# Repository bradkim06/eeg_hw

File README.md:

# Project Goal

기존 외주 뇌파모듈을 더 좋은 성능과 가격으로 대체

## Schematic

[v0.2-dev](./doc/eeg.pdf)

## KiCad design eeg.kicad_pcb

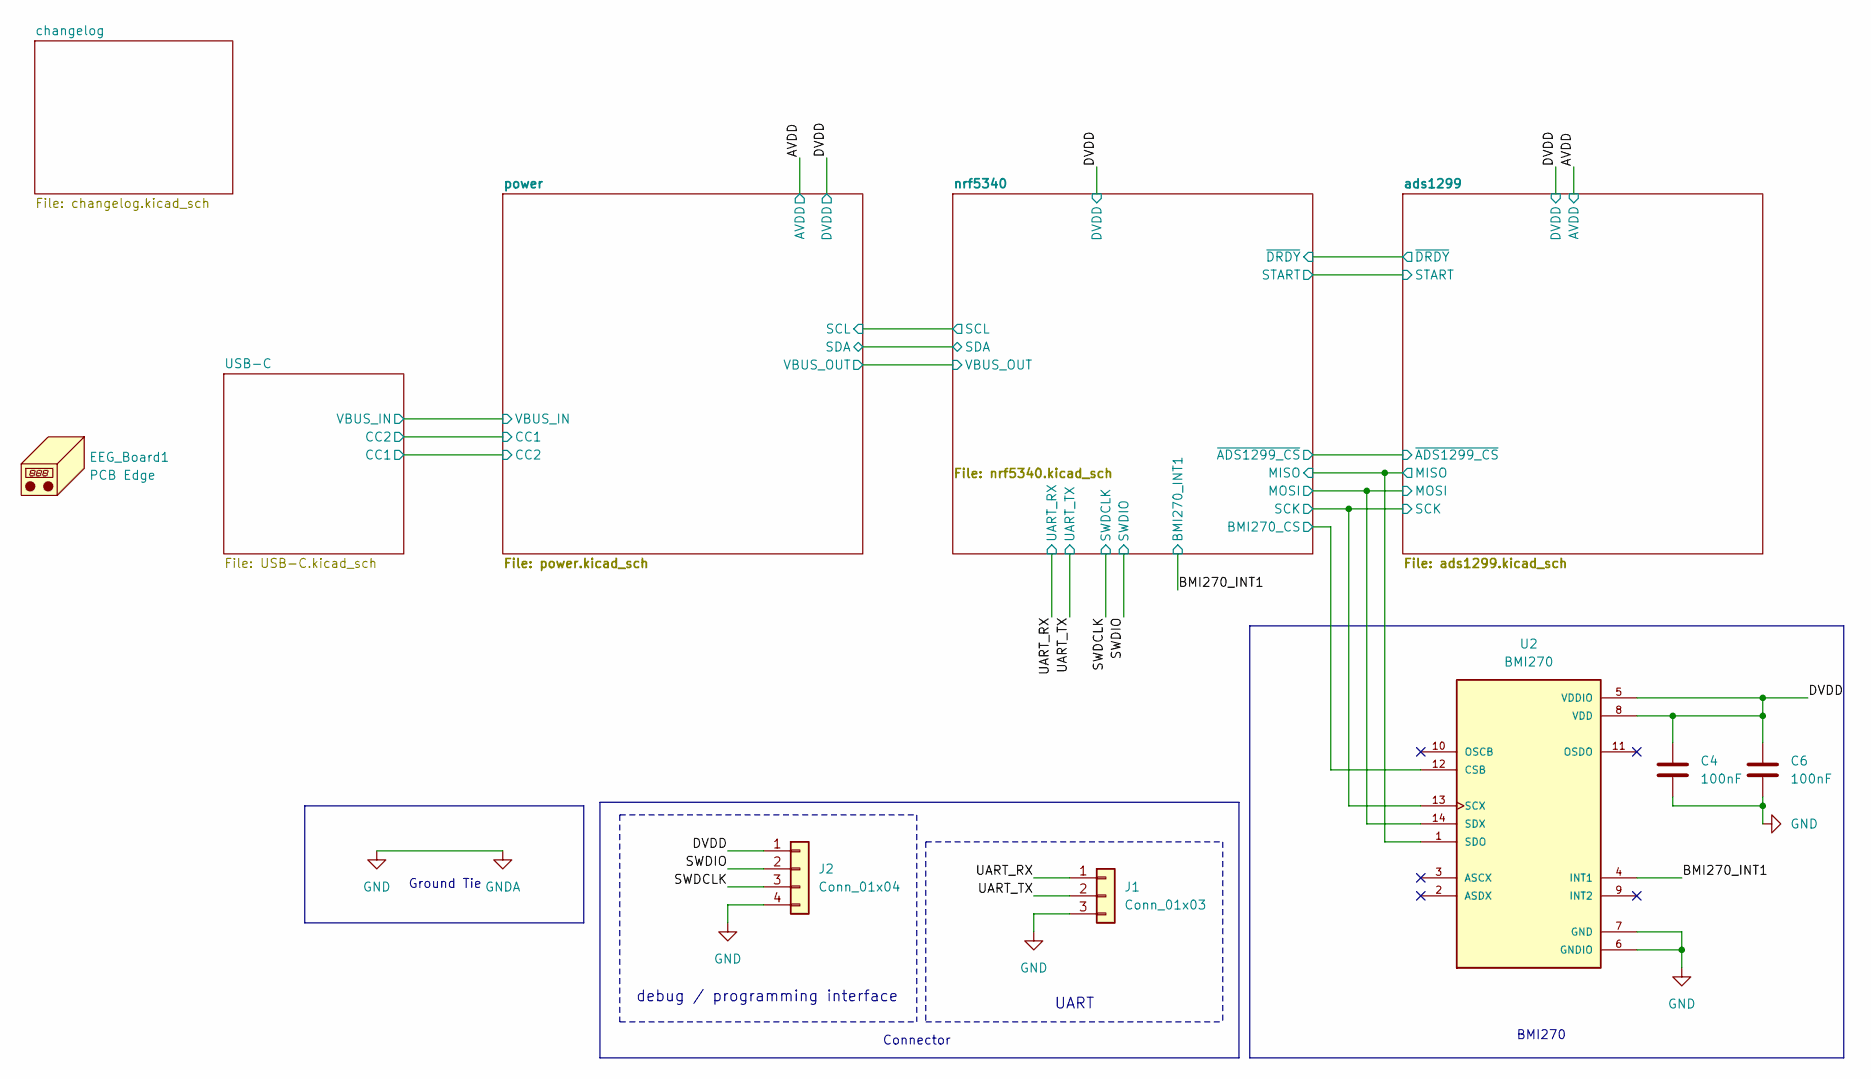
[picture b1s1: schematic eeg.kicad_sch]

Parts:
C4, C6: 100nF; C_0402_1005Metric; MANUFACTURER_PART_NUMBER GRM155R71C104KA88D
EEG_Board1: PCB Edge; eeg
J1: Conn_01x03; PinHeader_1x03_P2.54mm_Vertical; MANUFACTURER_PART_NUMBER 1.25T-3A
J2: Conn_01x04; PinHeader_1x04_P2.54mm_Vertical; MANUFACTURER_PART_NUMBER 1.25T-4A
U2: BMI270; XDCR_BMI270; MANUFACTURER_PART_NUMBER BMI270

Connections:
/BMI270_INT1: U2.4 (INT1); also elsewhere on the board
/DVDD: C4.1, C6.1, J2.1, U2.5 (VDDIO), U2.8 (VDD); also elsewhere on the board
/SWDCLK: J2.3; also elsewhere on the board
/SWDIO: J2.2; also elsewhere on the board
/UART_RX: J1.1; also elsewhere on the board
/UART_TX: J1.2; also elsewhere on the board
/ads1299/MISO: U2.1 (SDO); also elsewhere on the board
/ads1299/MOSI: U2.14 (SDX); also elsewhere on the board
/ads1299/SCK: U2.13 (SCX); also elsewhere on the board
/nrf5340/BMI270_CS: U2.12 (CSB); also elsewhere on the board
GND: C4.2, C6.2, J1.3, J2.4, U2.6 (GNDIO), U2.7 (GND); also elsewhere on the board

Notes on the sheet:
Ground Tie
UART
Connector
BMI270
debug / programming interface

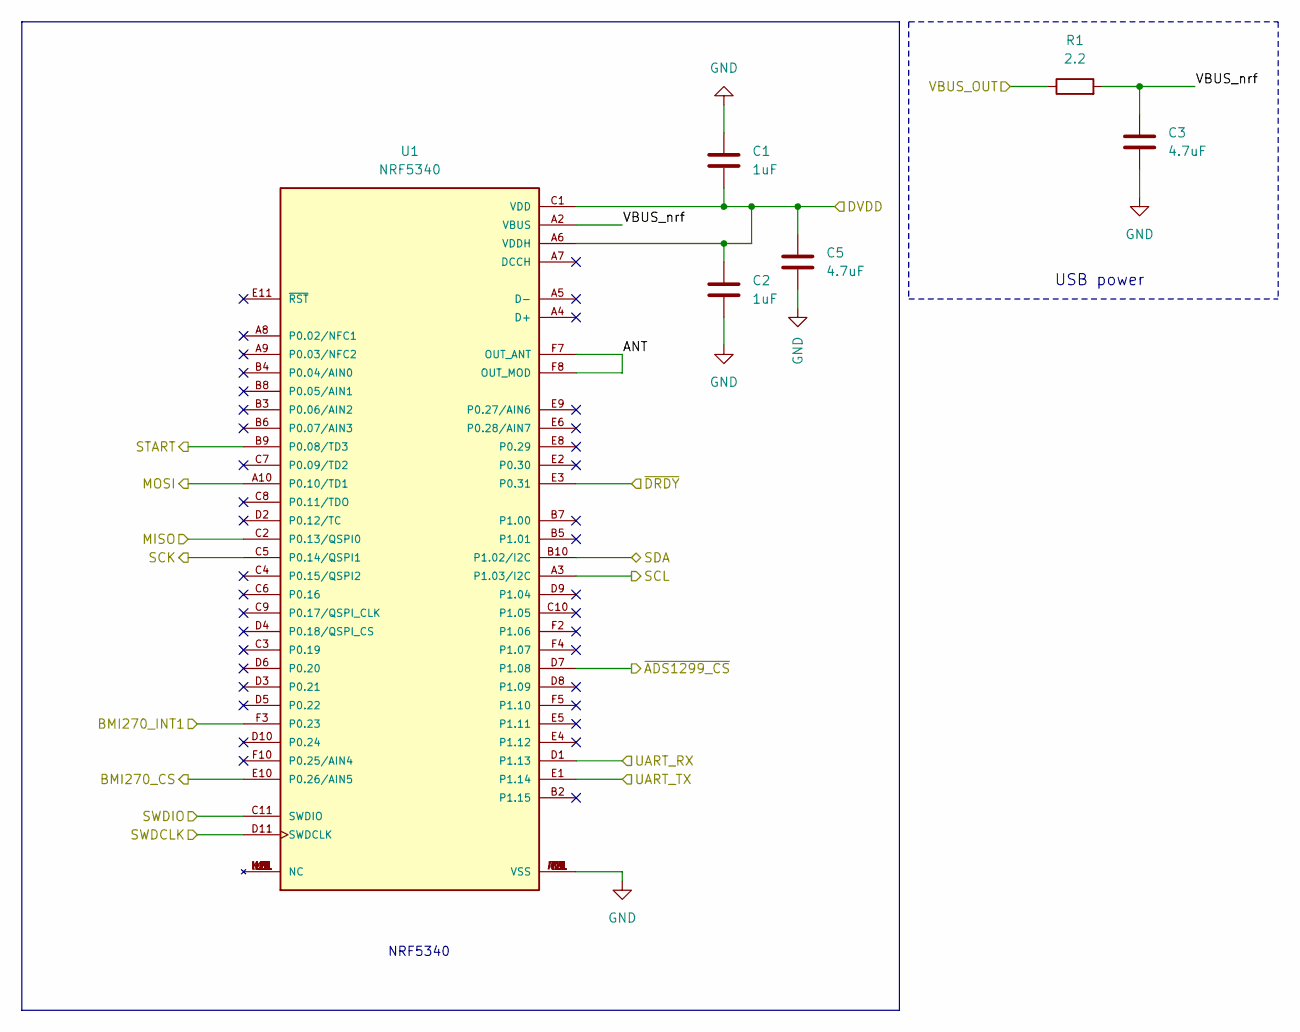
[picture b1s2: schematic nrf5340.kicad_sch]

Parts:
C1, C2: 1uF; C_0402_1005Metric; MANUFACTURER_PART_NUMBER GRM155R61A105KE15D
C3, C5: 4.7uF; C_0402_1005Metric; MANUFACTURER_PART_NUMBER GRM155R61A475MEAAD
R1: 2.2; R_0402_1005Metric; MANUFACTURER_PART_NUMBER RC0402FR-072R2L
U1: NRF5340; XCVR_ISP2053-AX-RS; PARTREV R6

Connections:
/BMI270_INT1: U1.F3 (P0.23); also elsewhere on the board
/DVDD: C1.2, C2.1, C5.1, U1.A6 (VDDH), U1.C1 (VDD); also elsewhere on the board
/SWDCLK: U1.D11 (SWDCLK); also elsewhere on the board
/SWDIO: U1.C11 (SWDIO); also elsewhere on the board
/UART_RX: U1.D1 (P1.13); also elsewhere on the board
/UART_TX: U1.E1 (P1.14); also elsewhere on the board
/ads1299/MISO: U1.C2 (P0.13/QSPI0); also elsewhere on the board
/ads1299/MOSI: U1.A10 (P0.10/TD1); also elsewhere on the board
/ads1299/SCK: U1.C5 (P0.14/QSPI1); also elsewhere on the board
/ads1299/START: U1.B9 (P0.08/TD3); also elsewhere on the board
/ads1299/~ADS1299_CS: U1.D7 (P1.08); also elsewhere on the board
/ads1299/~DRDY: U1.E3 (P0.31); also elsewhere on the board
/nrf5340/ANT: U1.F7 (OUT_ANT), U1.F8 (OUT_MOD)
/nrf5340/BMI270_CS: U1.E10 (P0.26/AIN5); also elsewhere on the board
/nrf5340/SCL: U1.A3 (P1.03/I2C); also elsewhere on the board
/nrf5340/SDA: U1.B10 (P1.02/I2C); also elsewhere on the board
/nrf5340/VBUS_OUT: R1.1; also elsewhere on the board
/nrf5340/VBUS_nrf: C3.1, R1.2, U1.A2 (VBUS)
GND: C1.1, C2.2, C3.2, C5.2, U1.A1 (VSS), U1.A11 (VSS), U1.E7 (VSS), U1.F1 (VSS), U1.F6 (VSS), U1.F9 (VSS), U1.F11 (VSS); also elsewhere on the board

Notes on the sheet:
NRF5340
USB power

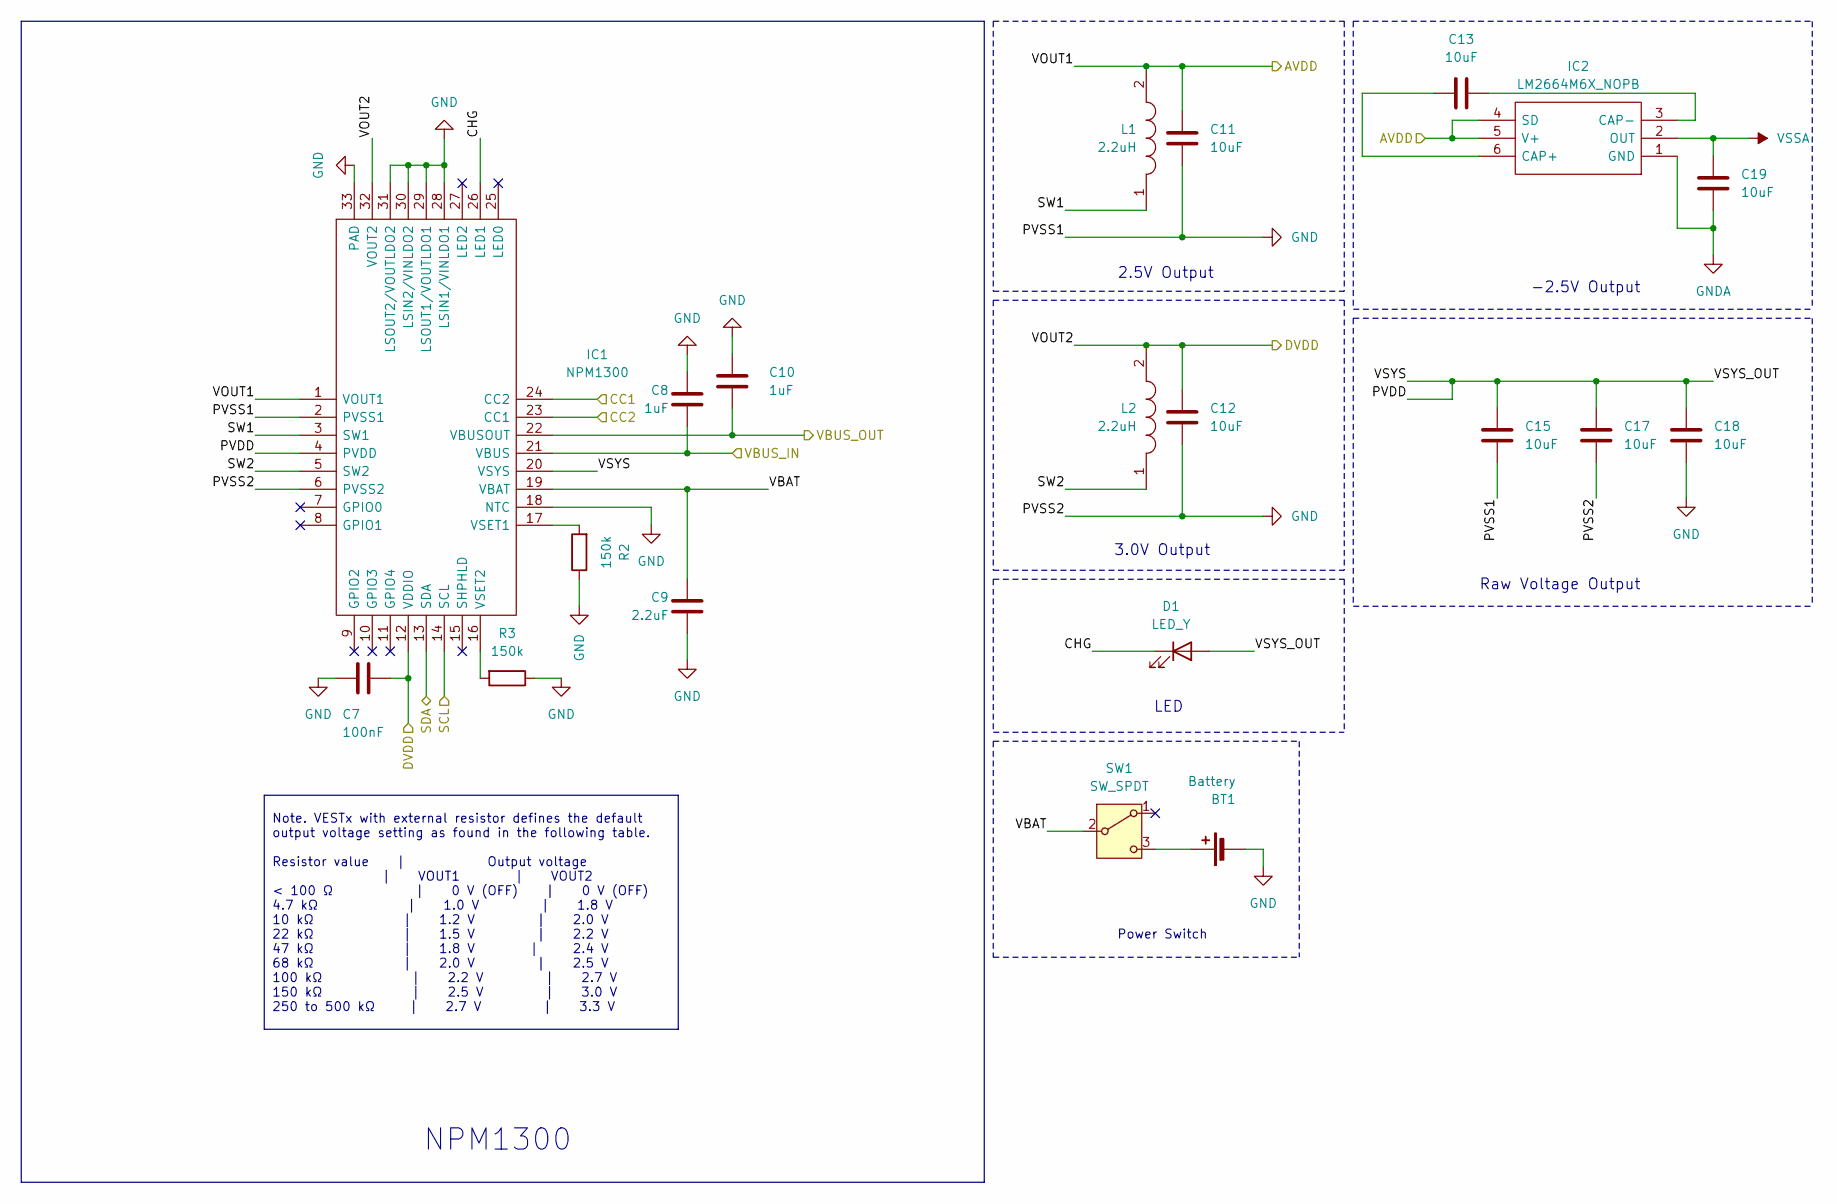
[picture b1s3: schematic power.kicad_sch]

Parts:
BT1: Battery; PinHeader_1x02_P1.27mm_Vertical; MANUFACTURER_PART_NUMBER 1.25T-2A
C7: 100nF; C_0402_1005Metric; MANUFACTURER_PART_NUMBER GRM155R71C104KA88D
C8, C10: 1uF; C_0402_1005Metric; MANUFACTURER_PART_NUMBER GRM155R61A105KE15D
C9: 2.2uF; C_0402_1005Metric; MANUFACTURER_PART_NUMBER GRM155Z71A225KE01D
C11, C12, C13, C15, C17, C18, C19: 10uF; C_0402_1005Metric; MANUFACTURER_PART_NUMBER GRM155R61A106ME44D
D1: LED_Y; LED_0603_1608Metric; MANUFACTURER_PART_NUMBER 19-213/Y2C-CQ2R2L/3T(CY)
IC1: NPM1300; QFN50P500X500X90-33N; Manufacturer_Part_Number NPM1300-QEAA-R; Mouser Part Number 949-NPM1300-QEAA-R
IC2: LM2664M6X_NOPB; SOT95P280X145-6N; Manufacturer_Part_Number LM2664M6X/NOPB; Mouser Part Number 926-LM2664M6X/NOPB
L1, L2: 2.2uH; INDC2016X100N; Manufacturer_Part_Number MLP2016H2R2MT0S1; Mouser Part Number 810-MLP2016H2R2MT0S1
R2, R3: 150k; R_0402_1005Metric; MANUFACTURER_PART_NUMBER RC0402FR-07150KL
SW1: SW_SPDT; MK-12C02-G020_GSW; MANUFACTURER_PART_NUMBER MK-12C02-G020

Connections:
/AVDD: C11.2, IC1.1 (VOUT1), IC2.4 (SD), IC2.5 (V+), L1.2; also elsewhere on the board
/DVDD: C7.1, C12.2, IC1.12 (VDDIO), IC1.32 (VOUT2), L2.2; also elsewhere on the board
/USB-C/CC1: IC1.23 (CC1); also elsewhere on the board
/USB-C/CC2: IC1.24 (CC2); also elsewhere on the board
/USB-C/VBUS_IN: C8.1, IC1.21 (VBUS); also elsewhere on the board
/nrf5340/SCL: IC1.14 (SCL); also elsewhere on the board
/nrf5340/SDA: IC1.13 (SDA); also elsewhere on the board
/nrf5340/VBUS_OUT: C10.1, IC1.22 (VBUSOUT); also elsewhere on the board
/power/CHG: D1.1 (K), IC1.26 (LED1)
/power/PVDD: C15.2, C17.2, C18.2, D1.2 (A), IC1.4 (PVDD), IC1.20 (VSYS)
/power/SW1: IC1.3 (SW1), L1.1
/power/SW2: IC1.5 (SW2), L2.1
/power/VBAT: C9.2, IC1.19 (VBAT), SW1.2 (B)
GND: BT1.2 (-), C7.2, C8.2, C9.1, C10.2, C11.1, C12.1, C15.1, C17.1, C18.1, C19.1, IC1.2 (PVSS1), IC1.6 (PVSS2), IC1.18 (NTC), IC1.28 (LSIN1/VINLDO1), IC1.29 (LSOUT1/VOUTLDO1), IC1.30 (LSIN2/VINLDO2), IC1.31 (LSOUT2/VOUTLDO2), IC1.33 (PAD), IC2.1 (GND), R2.1, R3.1; also elsewhere on the board
unnamed: BT1.1 (+), SW1.3 (C)
unnamed: IC1.17 (VSET1), R2.2
unnamed: IC1.16 (VSET2), R3.2
unnamed: C13.1, IC2.6 (CAP+)
unnamed: C13.2, IC2.3 (CAP-)
VSSA: C19.2, IC2.2 (OUT); also elsewhere on the board

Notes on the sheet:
Note. VESTx with external resistor defines the default output voltage setting as found in the following table. Resistor value | Output voltage | VOUT1 | VOUT2 < 100 Ω | 0 V (OFF) | 0 V (OFF) 4.7 kΩ | 1.0 V | 1.8 V 10 kΩ | 1.2 V | 2.0 V 22 kΩ | 1.5 V | 2.2 V 47 kΩ | 1.8 V | 2.4 V 68 kΩ | 2.0 V | 2.5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
-2.5V Output
Raw Voltage Output
3.0V Output
Power Switch
2.5V Output
LED
NPM1300

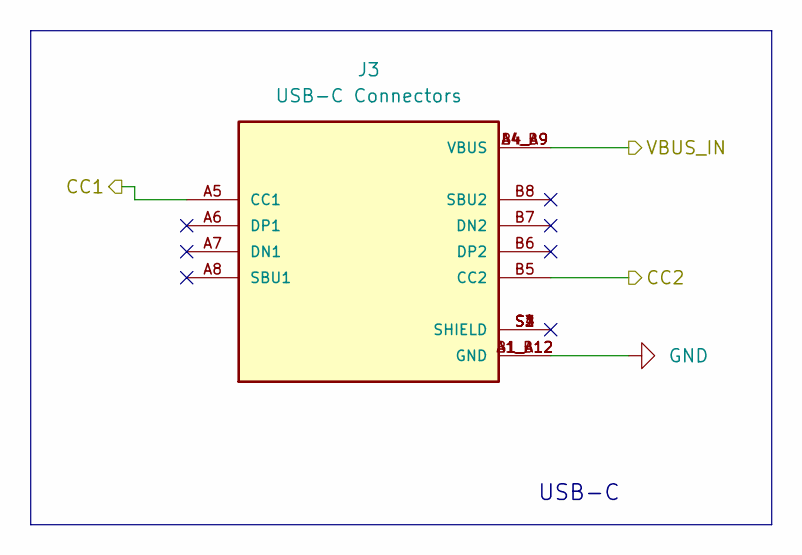
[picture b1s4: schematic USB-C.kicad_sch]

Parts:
J3: USB-C Connectors; HRO_TYPE-C-31-M-12; PARTREV 2020.12.08

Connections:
/USB-C/CC1: J3.A5 (CC1); also elsewhere on the board
/USB-C/CC2: J3.B5 (CC2); also elsewhere on the board
/USB-C/VBUS_IN: J3.A4_B9 (VBUS), J3.B4_A9 (VBUS); also elsewhere on the board
GND: J3.A1_B12 (GND), J3.B1_A12 (GND); also elsewhere on the board

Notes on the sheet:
USB-C

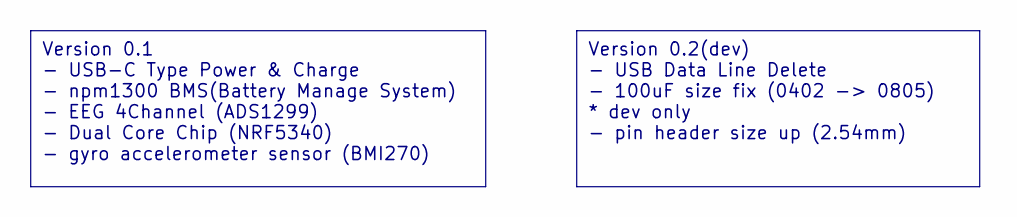
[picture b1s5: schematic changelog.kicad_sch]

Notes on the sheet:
Version 0.2(dev) - USB Data Line Delete - 100uF size fix (0402 -> 0805) * dev only - pin header size up (2.54mm)
Version 0.1 - USB-C Type Power & Charge - npm1300 BMS(Battery Manage System) - EEG 4Channel (ADS1299) - Dual Core Chip (NRF5340) - gyro accelerometer sensor (BMI270)

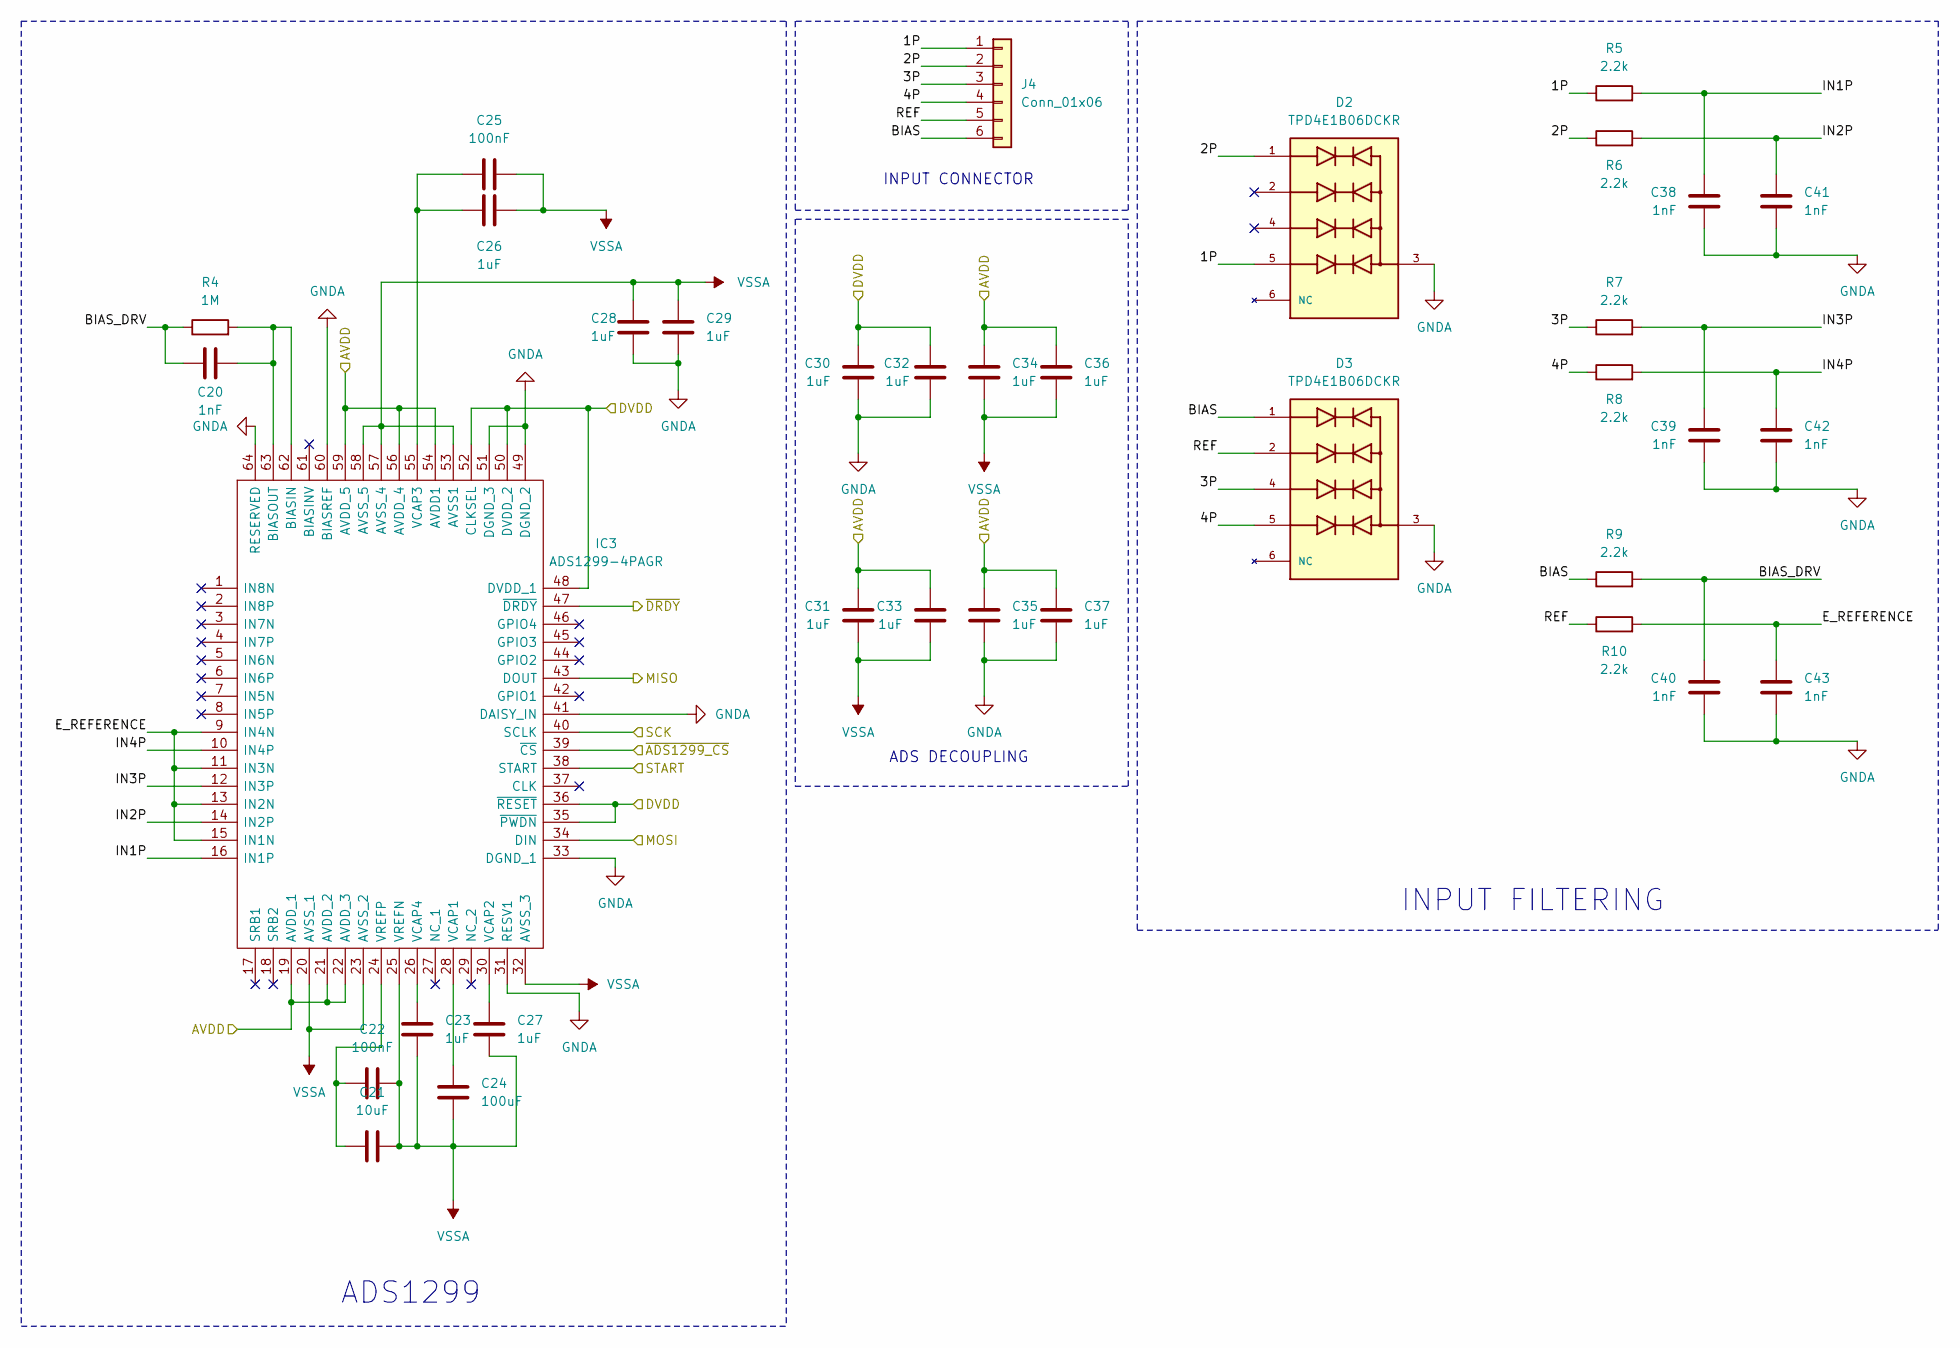
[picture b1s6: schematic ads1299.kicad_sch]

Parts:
C20, C38, C39, C40, C41, C42, C43: 1nF; C_0402_1005Metric; MANUFACTURER_PART_NUMBER GRM155R71H102KA01D
C21: 10uF; C_0402_1005Metric; MANUFACTURER_PART_NUMBER GRM155R61A106ME44D
C22, C25: 100nF; C_0402_1005Metric; MANUFACTURER_PART_NUMBER GRM155R71C104KA88D
C23, C26, C27, C28, C29, C30, C31, C32, C33, C34, C35, C36, C37: 1uF; C_0402_1005Metric; MANUFACTURER_PART_NUMBER GRM155R61A105KE15D
C24: 100uF; C_0805_2012Metric; MANUFACTURER_PART_NUMBER GRM21BR60J107ME15L
D2, D3: TPD4E1B06DCKR; TVS_TPD4E1B06DCKR; PARTREV C
IC3: ADS1299-4PAGR; QFP50P1200X1200X120-64N; Manufacturer_Part_Number ADS1299-4PAGR; Mouser Part Number 595-ADS1299-4PAGR
J4: Conn_01x06; PinHeader_1x06_P2.54mm_Vertical; MANUFACTURER_PART_NUMBER 1.25T-6A
R4: 1M; R_0402_1005Metric; MANUFACTURER_PART_NUMBER RC0402FR-071ML
R5, R6, R7, R8, R9, R10: 2.2k; R_0402_1005Metric; MANUFACTURER_PART_NUMBER RC0402FR-072K2L

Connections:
/AVDD: C31.2, C33.2, C34.2, C35.2, C36.2, C37.2, IC3.19 (AVDD_1), IC3.21 (AVDD_2), IC3.22 (AVDD_3), IC3.54 (AVDD1), IC3.56 (AVDD_4), IC3.59 (AVDD_5); also elsewhere on the board
/DVDD: C30.2, C32.2, IC3.35 (~PWDN), IC3.36 (~RESET), IC3.48 (DVDD_1), IC3.50 (DVDD_2), IC3.52 (CLKSEL); also elsewhere on the board
/ads1299/1P: D2.5, J4.1, R5.1
/ads1299/2P: D2.1, J4.2, R6.1
/ads1299/3P: D3.4, J4.3, R7.1
/ads1299/4P: D3.5, J4.4, R8.1
/ads1299/BIAS: D3.1, J4.6, R9.1
/ads1299/BIAS_DRV: C20.1, C40.2, R4.1, R9.2
/ads1299/E_REFERENCE: C43.2, IC3.9 (IN4N), IC3.11 (IN3N), IC3.13 (IN2N), IC3.15 (IN1N), R10.2
/ads1299/IN1P: C38.2, IC3.16 (IN1P), R5.2
/ads1299/IN2P: C41.2, IC3.14 (IN2P), R6.2
/ads1299/IN3P: C39.2, IC3.12 (IN3P), R7.2
/ads1299/IN4P: C42.2, IC3.10 (IN4P), R8.2
/ads1299/MISO: IC3.43 (DOUT); also elsewhere on the board
/ads1299/MOSI: IC3.34 (DIN); also elsewhere on the board
/ads1299/REF: D3.2, J4.5, R10.1
/ads1299/SCK: IC3.40 (SCLK); also elsewhere on the board
/ads1299/START: IC3.38 (START); also elsewhere on the board
/ads1299/~ADS1299_CS: IC3.39 (~CS); also elsewhere on the board
/ads1299/~DRDY: IC3.47 (~DRDY); also elsewhere on the board
GND: C28.1, C29.1, C30.1, C32.1, C35.1, C37.1, C38.1, C39.1, C40.1, C41.1, C42.1, C43.1, D2.3, D3.3, IC3.31 (RESV1), IC3.33 (DGND_1), IC3.41 (DAISY_IN), IC3.49 (DGND_2), IC3.51 (DGND_3), IC3.60 (BIASREF), IC3.64 (RESERVED); also elsewhere on the board
unnamed: C20.2, IC3.62 (BIASIN), IC3.63 (BIASOUT), R4.2
unnamed: C24.1, IC3.28 (VCAP1)
unnamed: C27.1, IC3.30 (VCAP2)
unnamed: C25.1, C26.1, IC3.55 (VCAP3)
unnamed: C23.1, IC3.26 (VCAP4)
unnamed: C21.2, C22.1, IC3.24 (VREFP)
VSSA: C21.1, C22.2, C23.2, C24.2, C25.2, C26.2, C27.2, C28.2, C29.2, C31.1, C33.1, C34.1, C36.1, IC3.20 (AVSS_1), IC3.23 (AVSS_2), IC3.25 (VREFN), IC3.32 (AVSS_3), IC3.53 (AVSS1), IC3.57 (AVSS_4), IC3.58 (AVSS_5); also elsewhere on the board

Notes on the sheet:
ADS DECOUPLING
ADS1299
INPUT CONNECTOR
INPUT FILTERING

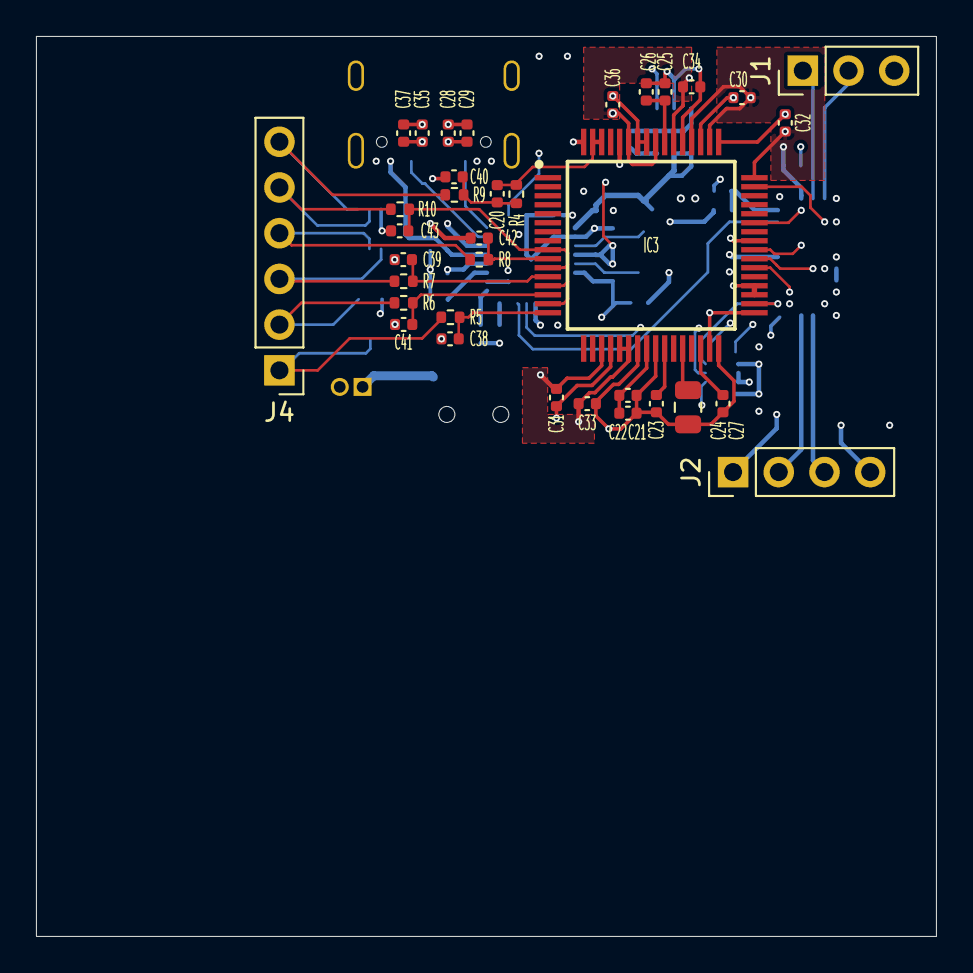
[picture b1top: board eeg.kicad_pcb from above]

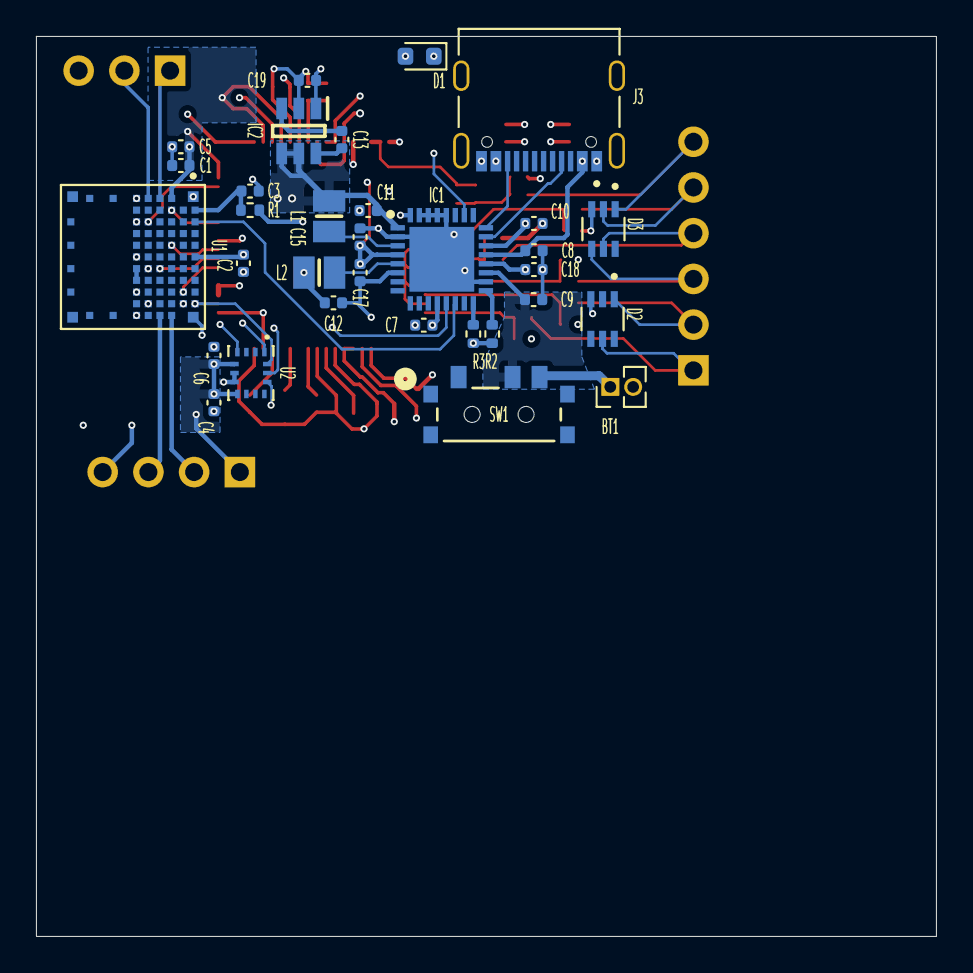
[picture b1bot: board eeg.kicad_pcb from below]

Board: 6 copper layers, 50.0 x 50.0 mm, 67 parts (32 on the bottom side), 52 nets.

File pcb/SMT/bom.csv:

"Reference","Qty","Value","MANUFACTURER","MANUFACTURER_PART_NUMBER","설명","Package","Type"
"C1,C2,C8,C10,C23,C26,C27,C28,C29,C30,C31,C32,C33,C34,C35,C36,C37","17","1uF","Murata Electronics","GRM155R61A105KE15D","10V 1uF X5R ±10% 0402  Multilayer Ceramic Capacitors MLCC - SMD/SMT ROHS","0402 (1005 Metric)","Surface Mount "
"C3,C5","2","4.7uF","Murata Electronics","GRM155R61A475MEAAD","10V 4.7uF X5R ±20% 0402  Multilayer Ceramic Capacitors MLCC - SMD/SMT ROHS","0402 (1005 Metric)","Surface Mount "
"C4,C6,C7,C22,C25","5","100nF","Murata Electronics","GRM155R71C104KA88D","16V 100nF X7R ±10% 0402  Multilayer Ceramic Capacitors MLCC - SMD/SMT ROHS","0402 (1005 Metric)","Surface Mount "
"C9","1","2.2uF","Murata Electronics","GRM155Z71A225KE01D","10V 2.2uF X7R ±10% 0402  Multilayer Ceramic Capacitors MLCC - SMD/SMT ROHS","0402 (1005 Metric)","Surface Mount "
"C11,C12,C13,C15,C17,C18,C19,C21","8","10uF","Murata Electronics","GRM155R61A106ME44D","10V 10uF X5R ±20% 0402  Multilayer Ceramic Capacitors MLCC - SMD/SMT ROHS","0402 (1005 Metric)","Surface Mount "
"C20,C38,C39,C40,C41,C42,C43","7","1nF","Murata Electronics","GRM155R71H102KA01D","50V 1nF X7R ±10% 0402  Multilayer Ceramic Capacitors MLCC - SMD/SMT ROHS","0402 (1005 Metric)","Surface Mount "
"C24","1","100uF","Murata Electronics","GRM21BR60J107ME15L","6.3V 100uF X5R ±20% 0805 Multilayer Ceramic Capacitors MLCC - SMD/SMT ROHS ","0805 (2012 Metric)","Surface Mount "
"D1","1","LED_Y","Everlight Elec","19-213/Y2C-CQ2R2L/3T(CY)","20mA -40℃~+85℃ 585.5nm~591.5nm Yellow 120° 60mW 0603  Light Emitting Diodes (LED) ROHS","0603 (1608 Metric)","Surface Mount "
"D2,D3","2","TPD4E1B06DCKR","Texas Instruments","TPD4E1B06DCKR","SOT-363  Electrostatic and Surge Protection (TVS/ESD) ROHS","SOT-363","Surface Mount "
"IC1","1","NPM1300","NORDIC SEMICONDUCTOR","nPM1300-QEAA-R","Battery Management Power Management IC (PMIC) with unique system management features, QFN32","QFN-32","Surface Mount "
"IC2","1","LM2664M6X_NOPB","Texas Instruments ","LM2664M6X/NOPB ","Switching Voltage Regulators Switched Capacitor Vtg Cnvtr","SOT-23-6","Surface Mount "
"IC3","1","ADS1299-4PAGR","Texas Instruments ","ADS1299-4PAGR","Analog to Digital Converters - ADC Low-Noise, 4-Channel, 24-Bit Analog-to-Digital Converter for Biopotential Measurements","TQFP-64","Surface Mount "
"J3","1","USB-C Connectors","Korean Hroparts Elec","TYPE-C-31-M-12","5A 1 16P Female Type-C SMD USB Connectors ROHS ","SMD","Surface Mount "
"L1,L2","2","2.2uH","TDK Corporation","MLP2016H2R2MT0S1","SMD / SMT Inductors (Coils), L=2.2?H, L x W x T :","0806 (2016 Metric)","Surface Mount "
"R1","1","2.2","YAGEO","RC0402FR-072R2L","62.5mW Thick Film Resistors 50V ±1% ±200ppm/℃ 2.2Ω 0402  Chip Resistor - Surface Mount ROHS","0402 (1005 Metric)","Surface Mount "
"R2,R3","2","150k","YAGEO","RC0402FR-07150KL","62.5mW Thick Film Resistors 50V ±100ppm/℃ ±1% 150kΩ 0402  Chip Resistor - Surface Mount ROHS","0402 (1005 Metric)","Surface Mount "
"R4","1","1M","YAGEO","RC0402FR-071ML","62.5mW Thick Film Resistors 50V ±100ppm/℃ ±1% 1MΩ 0402  Chip Resistor - Surface Mount ROHS","0402 (1005 Metric)","Surface Mount "
"R5,R6,R7,R8,R9,R10","6","2.2k","YAGEO","RC0402FR-072K2L","62.5mW Thick Film Resistors 50V ±100ppm/℃ ±1% 1MΩ 0402  Chip Resistor - Surface Mount ROHS","0402 (1005 Metric)","Surface Mount "
"SW1","1","SW_SPDT","G-Switch","MK-12C02-G020","Right Angle 1A SPDT 6V Black Slide Switches ROHS","SMD","Surface Mount"
"U1","1","NRF5340","InsightSIP","ISP2053-AX-RS","Bluetooth Modules - 802.15.1 ISP2053-AX nRF5340 Bluetooth 5.2 LE Audio, DF and Long Range Module","LGA-75","Surface Mount "
"U2","1","BMI270","Bosch Sensortec","BMI270","Attitude Sensor/Gyroscope","LGA-14","Surface Mount "

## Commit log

2024-05-29 first init
2024-05-29 README & changelog init
2024-05-29 사용하지 않는 폴더 제거(gerber)
2024-05-29 schematic pdf init
2024-05-29 사용하지 않는 파일 제거
2024-05-30 한샘디지텍 견적전 최종수정
    - Reference Circuit 확인
    - bom 갱신
    - EMC Layout 확인
    - ERC 확인
    - Gerber
    - SMT 요청서
2024-06-13 한샘디지텍 견적전 수정
    - Reference Circuit 확인
    - bom 갱신
    - EMC Layout 확인
    - ERC 확인
    - Gerber
    - SMT 요청서
2024-06-13 Feat: 개발보드 버전으로 PCB 변경
    수정사항
    단가 감소
    - PCB Board size up (50x50)
    - blind via 제거 (전체 레이아웃 수정)
    - AVDD 전력평면 추가
    - ADS1299 안쓰는핀 GND
2024-06-13 Doc: Gerber Data V0.2(dev)
2024-06-18 Doc: schematic PDF 추가
2024-06-20 Doc: Gerber Refresh
